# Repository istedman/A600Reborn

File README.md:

# A600Reborn

Amiga A600 schematics recaptured in KiCad and a new PCB design created from them. 
There is currently one, working, version which replaces the RF modulator with a mini-DIN for S-video.

Schematics and baseline PCB captured by Mick @ EAB. Checked and updated by myself.

Original thread is here: http://eab.abime.net/showthread.php?t=98176

<B>Status as of 23rd February 2021</B><P>
  
The Baseline version is still undergoing testing and is currently not fully functioning, this vairant is not published here.
Use the A600_S_Video branch if you want to try the working variant.

The S-Video variant, which was tracked via manual methods, rather than auto-routed, currently works and boots.
<B> Photos of the S-Video variant<B>

Wiki will be updated with debug/test information.

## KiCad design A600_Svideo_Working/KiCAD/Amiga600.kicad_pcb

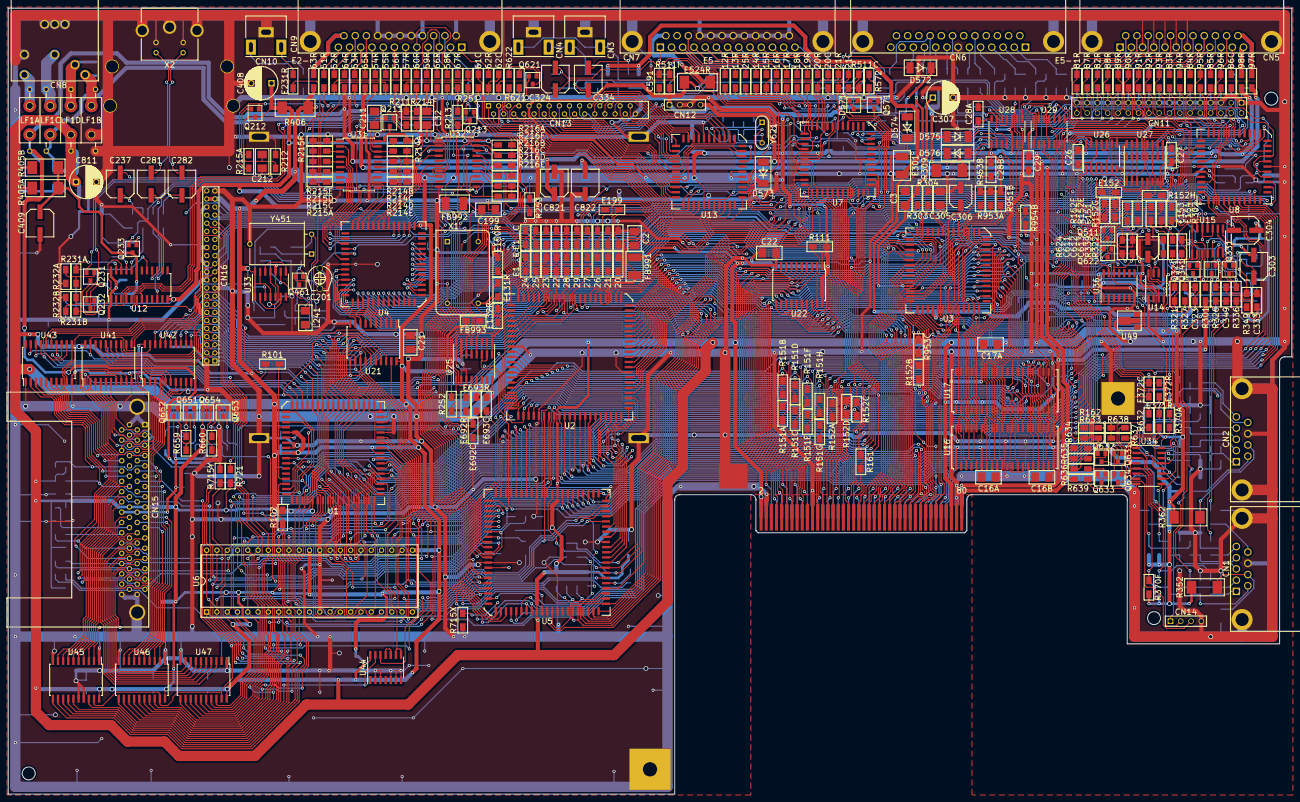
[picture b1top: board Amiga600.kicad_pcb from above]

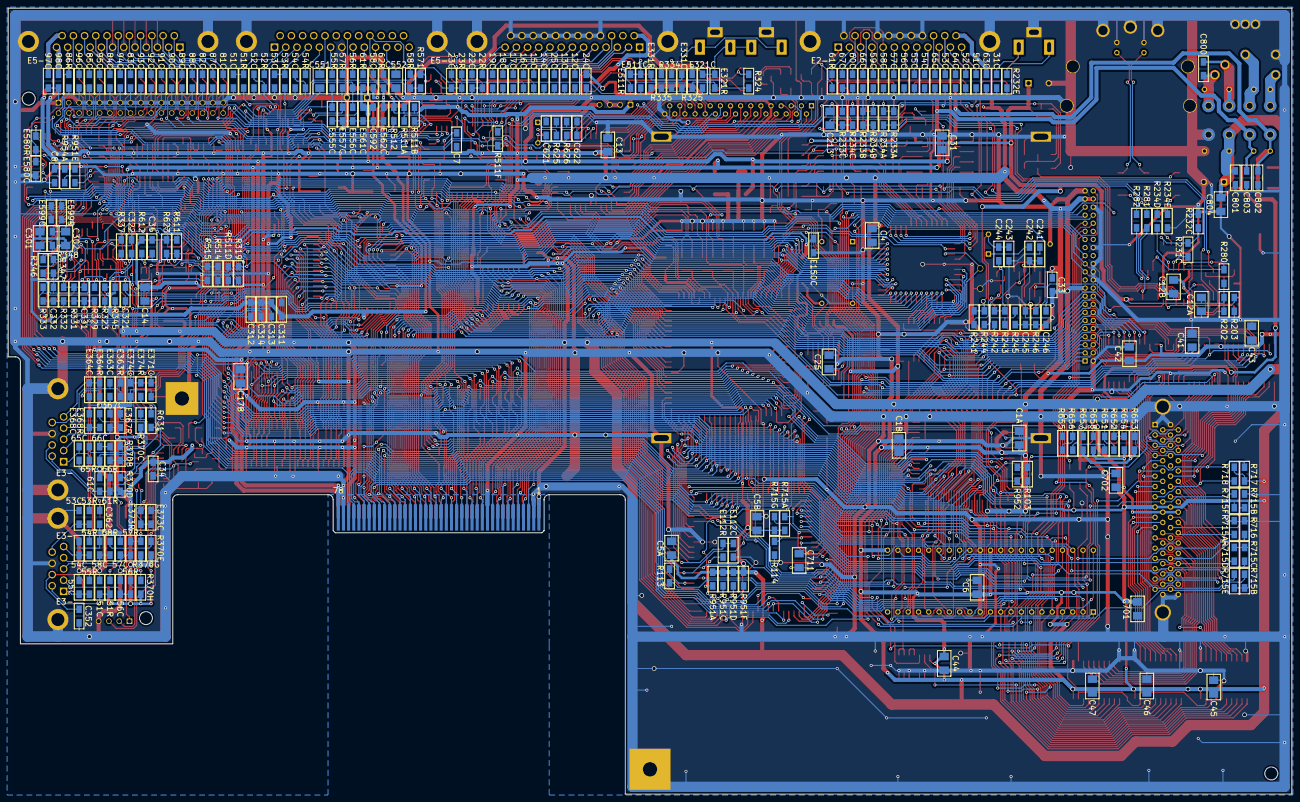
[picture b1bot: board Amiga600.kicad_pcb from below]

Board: 2 copper layers, 317.0 x 194.1 mm, 575 parts (259 on the bottom side), 566 nets.

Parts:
C2, C3, C4, C6, C13, C14, C21, C22, C25, C31, C32, C41, C42, C43, C44, C45, C46, C47, C199, C211, C212, C213, C301, C302, C305, C551, C552, C701, C702, C711, C804: 0.33uF; SMD_1210
C7, C8, C26, C27, C29, C33, C34, C36, C244, C246, C349, C591, C592, C613, C800, C801, C802, C803: 0.01uF; SMD_1206
C201: 47pf*; Trimmer
C237, C281, C282: 220uF; C_SMD_D6.3
C241, C245: 56pF; SMD_1206
C242: 15pF; SMD_1206
C243: 1000pF; SMD_1206
C303, C304, C324, C334: 22uF; C_SMD_D6.3
C306, C612: 10uF; C_SMD_D5
C307: 470uF; C_RAD_P5
C311, C312, C313, C314, C352: 0.047uF; SMD_1206
C321, C323, C331, C333: 3900pF; SMD_1206
C322, C332: 6800pF; SMD_1206
C362, C611: 0.1uF; SMD_1206
C408, C811: 1000uF; C_RAD_P5
C409: 100uF; C_SMD_D6.3
C621, C622: 22pF; SMD_1206
C821, C822: 47uF; C_SMD_D6.3
CA1, CA5, CA12, CA16, CA17: 0.33uF; SMD_1210
CA28: 0.01uF; SMD_1206
CB1, CB5, CB12, CB16, CB17: 0.33uF; SMD_1210
CB28: 0.01uF; SMD_1206
CN1, CN2: DB9P
CN3, CN4, CN10: RCA
CN5: DB23S
CN6: DB25P
CN7: DB25S
CN8: POWER; Power
CN9: DB23P
CN11: FLOPPY; Floppy
CN12, CN14: 4PIN; 1x04_P2.54
CN13: KEYBOARD; FFC-30
CN15: PCMCIA
CN16: IDE
D571: 1N914; SOT-23_Diode
D572, D573, D574, D575, D576: 1N4001; SMD_MELF
E151, E152, E153, E154: 47pF; SMD_1206
E199: 27; SMD_1206
E301: FB; SMD_1812
EC112, EC122, EC123, EC124, EC125, EC126, EC127: 22pF; SMD_1206
EC120: 0.33uF; SMD_1206
EC121, EC262: *; SMD_1206
EC128, EC129, EC150, EC258, EC259, EC260, EC692, EC693: 47pF; SMD_1206
EC231, EC251, EC252, EC253, EC254, EC255, EC256, EC257, EC261, EC266, EC267, EC511, EC512, EC513, EC514, EC515, EC516, EC517, EC518, EC519, EC520, EC521, EC522, EC523, EC525, EC551, EC552, EC558, EC580, EC581, EC582, EC583, EC584, EC585, EC586, EC587, EC588, EC589, EC590, EC591, EC592, EC593, EC594, EC595, EC596, EC599: 100pF; SMD_1206
EC263, EC264, EC265, EC524, EC557, EC561, EC562, EC597, EC598: 0.01uF; SMD_1206
EC321, EC331, EC355, EC356, EC357, EC358, EC365, EC366, EC367, EC368: 6800pF; SMD_1206
EC351, EC353, EC354, EC361, EC363, EC364, EC371, EC372, EC373, EC374, EC553, EC554, EC555, EC556: 470pF; SMD_1206
ER112, ER122, ER123, ER124, ER125, ER128, ER129, ER150, ER580, ER583, ER584, ER585, ER587, ER590, ER591, ER592, ER593, ER594, ER595, ER599: 27; SMD_1206
ER120, ER321, ER331: 0; SMD_1206
ER121: *; SMD_1206
ER126, ER127, ER253, ER254, ER255, ER256, ER557, ER561, ER562: 47; SMD_1206
ER131, ER132, ER251, ER252, ER257, ER261, ER262, ER266, ER267, ER351, ER353, ER354, ER355, ER356, ER357, ER358, ER361, ER363, ER364, ER365, ER366, ER367, ER368, ER371, ER372, ER373, ER374, ER511, ER512, ER513, ER514, ER515, ER516, ER517, ER518, ER519, ER520, ER521, ER522, ER523, ER525, ER551, ER552, ER553, ER554, ER555, ER556, ER558, ER581, ER582, ER586, ER588, ER589, ER596, ER692, ER693: 68; SMD_1206
ER231: FB100; SMD_1206
ER258, ER259, ER260, ER263, ER264, ER265, ER597, ER598: FB200; SMD_1206
ER524: 47; SMD_2512
FB991, FB992: FB; SMD_1812
FB993: FB; SMD_1206
H1, H2, H3: MountingHole; Hole
L241: 1.2uH; SMD_1210
LF1: FERRITE; Ferrite
MT1, MT2, MT3, MT4: MountingHole_Pad; MT1-4
MT5: MountingHole_Pad; MT5
MT6: MountingHole_Pad; MT6
MT7: MountingHole_Pad; MT7
P9: 80PIN; Expansion
Q211, Q212, Q213, Q231, Q232, Q233, Q461, Q511, Q571, Q621, Q622, Q651, Q653: 2N3904; SOT-23
Q321, Q331: MPF102; SOT-23
Q341, Q631, Q632, Q633, Q634, Q652, Q654: 2N3906; SOT-23
R101, R102, R103, R244, R303, R304, R319, R324, R334, R512, R621, R654: 1K; SMD_1206
R111, R161, R162, R515, R659, R660, R952: 470; SMD_1206
R113, R114: 27; SMD_1206
R202, R246, R624, R625, R626, R658: *; SMD_1206
R203: 0; SMD_1206
R211, R212, R213: 150; SMD_1206
R241, R251, R252, R253, R348, R514, R632, R634, R636, R638, R651, R655, R721: 4.7K; SMD_1206
R242: 6.8K; SMD_1206
R243, R322, R323, R327, R329, R332, R333, R337, R339, R346, R572, R623, R631, R633, R635, R637, R652, R653, R656, R657, R716, R717, R718: 10K; SMD_1206
R245, R347, R571: 2.7K; SMD_1206
R280: 2.61K; SMD_1206
R281, R282: 75; SMD_1206
R301, R302: 10; SMD_1206
R309: 1; SMD_2512
R321, R331: 680; SMD_1206
R325, R335: 2K; SMD_1206
R326, R336: 470K; SMD_1206
R345: 22K; SMD_1206
R349: 33K; SMD_1206
R352, R362, R406: 4.7; SMD_2512
R611: 1M; SMD_1206
R612: 47K; SMD_1206
R622, R639: 100; SMD_1206
RA151, RA152: 68; SMD_1206
RA214, RA215, RA216: 270; SMD_1206
RA231, RA954: 1K; SMD_1206
RA232: 33K; SMD_1206
RA233: 150; SMD_1206
RA234: 75; SMD_1206
RA370, RA951: 4.7K; SMD_1206
RA405: 1; SMD_2512
RA511, RA715: 10K; SMD_1206
RA714: 120; SMD_1206
RA953: 470; SMD_1206
RB151: 68; SMD_1206
RB152: 27; SMD_1206
RB214, RB215, RB216, RB231, RB954: 1K; SMD_1206
RB232: 33K; SMD_1206
RB233: 150; SMD_1206
RB234: 75; SMD_1206
RB370, RB951: 4.7K; SMD_1206
RB405: 1; SMD_2512
RB511, RB715: 10K; SMD_1206
RB714: 120; SMD_1206
RB953: 470; SMD_1206
RC151: 68; SMD_1206
RC152: 27; SMD_1206
RC214, RC215, RC216: 2K; SMD_1206
RC231: 1K; SMD_1206
RC232: 33K; SMD_1206
RC233: 150; SMD_1206
RC234: 75; SMD_1206
RC370, RC951: 4.7K; SMD_1206
RC511, RC715: 10K; SMD_1206
RC953: 470; SMD_1206
RD151: 68; SMD_1206
RD152: 27; SMD_1206
RD214, RD215, RD216: 4K; SMD_1206
RD234: 43; SMD_1206
RD370, RD951: 4.7K; SMD_1206
RD511: 1K; SMD_1206
RD715: 10K; SMD_1206
RE151: 68; SMD_1206
RE152: 27; SMD_1206
RE214, RE215, RE216: 8K; SMD_1206
RE232: 75; SMD_1206
RE234: 240; SMD_1206
RE370, RE951: 4.7K; SMD_1206
RE715: 10K; SMD_1206
RF151: 68; SMD_1206
RF152: 27; SMD_1206
RF214, RF215, RF216: 330; SMD_1206
RF370, RF951: 4.7K; SMD_1206
RF511, RF715: 10K; SMD_1206
RG151: 68; SMD_1206
RG152: 27; SMD_1206
RG370: 4.7K; SMD_1206
RG715: 10K; SMD_1206
RH151: 68; SMD_1206
RH152: 27; SMD_1206
RH370: 4.7K; SMD_1206
RI511: 10K; SMD_1206
RX715: 4.7K; SMD_1206
RY715: 4.7K; SMD_1206
U1: MC68000; PLCC-68
U2: AGNUS; PLCC-84
U3: PAULA; PLCC-52
U4: DENISE; PLCC-52
U5: GAYLE; PLCC-84
U6: ROM; DIP-42
U7, U8: 8520; PLCC-44
U12: CXA2075M; SOP-24
U13: 6570; PLCC-44
U14: NE555; SOIC-8
U15: TL084; SOIC-14
U16, U17: 256Kx16; SOJ-40
U21, U22, U41, U42, U43, U45, U46, U47: 74LS245; SOIC-20W
U25: 74F258; SOIC-16-DUAL
U26: 74F00; SOIC-14
U27: 74F139; SOIC-16-DUAL
U28: 1488; SOIC-14
U29: 1489; SOIC-14
U31, U32: 74HCT244; SOIC-20W
U33: 74LS74A; SOIC-14
U34: 74LS157; SOIC-16
U36: 74F27; SOIC-14
U44: 74F02; SOIC-14
U49: RH5VA43A; SOT-89
X1: 28.37516MHz; Oscillator
X2: MINI-DIN; S-Video
Y451: 4.433619MHz; Crystal
Y621: 3MHz; Resonator

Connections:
7MHz: EC123.2, ER123.2, U1.15
7MHz_A: C201.1, EC122.2, ER122.2, U4.38
14MHz: E199.2, EC121.2, ER121.2, U5.22
14MHz_A: EC120.2, ER120.2, P9.67
+5V: C4.1, C6.1, C7.1, C8.1, C13.1, C14.1, C21.1, C22.1, C26.1, C27.1, C29.1, C33.1, C34.1, C36.1, C41.1, C42.1, C43.1, C44.1, C45.1, C46.1, C47.1, C591.1, C701.1, C801.1, C804.1, C811.1, CA1.1, CA5.1, CA16.1, CA17.1, CB1.1, CB5.1, CB16.1, CB17.1, CN12.1, CN13.9, CN15.17, CN15.51, CN16.41, CN16.42, D572.1, D573.1, D574.1, EC524.2, ER263.2, ER524.2, ER598.1, FB991.1, FB992.1, FB993.1, LF1.8, P9.1, P9.2, P9.76, Q631.2, Q632.2, Q633.2, Q634.2, Q654.2, R101.1, R102.1, R103.1, R111.1, R251.1, R252.1, R253.1, R309.1, R319.2, R352.1, R362.1, R406.1, R512.1, R514.1, R611.1, R612.1, R623.1, R631.1, R633.1, R635.1, R637.1, R639.1, R658.1, R716.1, R717.1, R718.1, R721.1, R952.2, RA370.1, RA405.2, RA511.1, RA715.1, RA951.2, RA953.2, RA954.2, RB370.1, RB405.2, RB511.1, RB715.1, RB951.2, RB953.2, RB954.2, RC370.1, RC511.1, RC715.1, RC951.2, RC953.2, RD370.1, RD511.1, RD715.1, RD951.2, RE370.1, RE715.1, RE951.2, RF370.1, RF511.1, RF715.1, RF951.2, RG370.1, RG715.1, RH370.1, RI511.1, U1.14, U1.18, U1.31, U1.52, U4.21, U5.20, U5.62, U6.22, U6.32, U7.22, U8.22, U13.1, U13.24, U13.33, U13.44, U14.4, U14.8, U16.1, U16.6, U16.20, U17.1, U17.6, U17.20, U21.20, U22.20, U26.14, U27.16, U28.5, U28.10, U28.13, U29.14, U33.1, U33.4, U33.10, U33.13, U33.14, U34.16, U36.14, U41.20, U42.20, U43.20, U44.14, U45.20, U46.20, U47.20, U49.2
+12V: C592.1, C802.1, C821.1, CN12.4, D575.2, EC561.1, ER264.2, ER561.1, ER597.1, LF1.2, P9.79, Q652.2, R301.1, R653.1, R657.1
+AV: C301.1, C303.1, Q341.2, R301.2, R347.1, U15.4
+VID: C31.1, C32.1, C408.1, CA12.1, Q211.3, Q212.3, Q213.3, R202.1, R241.1, R244.1, R280.1, R406.2, RA214.1, RA215.1, RA216.1, U12.12, U31.20, U32.20
+VOUT: C409.1, CB12.1, Q231.3, Q232.3, Q233.3, RA405.1, RB405.1, U12.19
-12V: C803.2, C822.2, D576.1, EC562.1, ER265.2, ER562.1, LF1.6, P9.80, R302.2
-AV: C302.2, C304.2, R302.1, R348.2, U15.11
/06. Serial, Parallel/PPD0: ER512.1, U7.12
/06. Serial, Parallel/PPD1: ER513.1, U7.13
/06. Serial, Parallel/PPD2: ER514.1, U7.14
/06. Serial, Parallel/PPD3: ER515.1, U7.15
/06. Serial, Parallel/PPD4: ER516.1, U7.16
/06. Serial, Parallel/PPD5: ER517.1, U7.17
/06. Serial, Parallel/PPD6: ER518.1, U7.18
/06. Serial, Parallel/PPD7: ER519.1, U7.19
/10. PCMCIA/CC_A0: CN15.29, U45.2
/10. PCMCIA/CC_A1: CN15.28, U47.9
/10. PCMCIA/CC_A2: CN15.27, U47.8
/10. PCMCIA/CC_A3: CN15.26, U47.7
/10. PCMCIA/CC_A4: CN15.25, U47.6
/10. PCMCIA/CC_A5: CN15.24, U47.5
/10. PCMCIA/CC_A6: CN15.23, U47.4
/10. PCMCIA/CC_A7: CN15.22, U47.3
/10. PCMCIA/CC_A8: CN15.12, U47.2
/10. PCMCIA/CC_A9: CN15.11, U46.9
/10. PCMCIA/CC_A10: CN15.8, U46.8
/10. PCMCIA/CC_A11: CN15.10, U46.7
/10. PCMCIA/CC_A12: CN15.21, U46.6
/10. PCMCIA/CC_A13: CN15.13, U46.5
/10. PCMCIA/CC_A14: CN15.14, U46.4
/10. PCMCIA/CC_A15: CN15.20, U46.3
/10. PCMCIA/CC_A16: CN15.19, U46.2
/10. PCMCIA/CC_A17: CN15.46, U45.9
/10. PCMCIA/CC_A18: CN15.47, U45.8
/10. PCMCIA/CC_A19: CN15.48, U45.7
/10. PCMCIA/CC_A20: CN15.49, U45.6
/10. PCMCIA/CC_A21: CN15.50, U45.5
/10. PCMCIA/CC_A22: CN15.53, U45.4
/10. PCMCIA/CC_A23: CN15.54, U45.3
/10. PCMCIA/CC_A24: CN15.55, RB714.2
/10. PCMCIA/CC_A25: CN15.56, RA714.2
/10. PCMCIA/CC_D0: CN15.30, U41.9
/10. PCMCIA/CC_D1: CN15.31, U41.8
/10. PCMCIA/CC_D2: CN15.32, U41.7
/10. PCMCIA/CC_D3: CN15.2, U41.6
/10. PCMCIA/CC_D4: CN15.3, U41.5
/10. PCMCIA/CC_D5: CN15.4, U41.4
/10. PCMCIA/CC_D6: CN15.5, U41.3
/10. PCMCIA/CC_D7: CN15.6, U41.2
/10. PCMCIA/CC_D8: CN15.64, U42.9
/10. PCMCIA/CC_D9: CN15.65, U42.8
/10. PCMCIA/CC_D10: CN15.66, U42.7
/10. PCMCIA/CC_D11: CN15.37, U42.6
/10. PCMCIA/CC_D12: CN15.38, U42.5
/10. PCMCIA/CC_D13: CN15.39, U42.4
/10. PCMCIA/CC_D14: CN15.40, U42.3
/10. PCMCIA/CC_D15: CN15.41, U42.2
A1: U1.32, U2.60, U6.10, U47.11
A2: CN16.35, P9.57, U1.33, U2.61, U6.9, U47.12
A3: CN16.33, P9.58, U1.34, U2.62, U6.8, U47.13
A4: CN16.36, P9.59, U1.35, U2.63, U6.7, U47.14
A5: P9.60, U1.36, U2.64, U6.6, U47.15
A6: U1.37, U2.65, U6.5, U47.16
A7: U1.38, U2.66, U6.4, U47.17
A8: U1.39, U2.67, U6.3, U7.42, U8.42, U47.18
A9: U1.40, U2.68, U6.41, U7.41, U8.41, U46.11
A10: U1.41, U2.69, U6.40, U7.39, U8.39, U46.12
A11: U1.42, U2.70, U6.39, U7.38, U8.38, U46.13
A12: U1.43, U2.71, U5.41, U6.38, U46.14
A13: U1.44, U2.72, U5.42, U6.37, U46.15
A14: U1.45, U2.73, U5.43, U6.36, U46.16
A15: U1.46, U2.74, U5.44, U6.35, U46.17
A16: U1.47, U2.75, U5.46, U6.34, U44.8, U44.9, U46.18
A17: U1.48, U2.76, U5.47, U6.33, U45.11
A18: U1.49, U2.77, U5.48, U6.2, U45.12
A19: U1.50, U2.59, U5.49, U6.1, U45.13
A20: U1.51, U2.35, U5.50, U6.42, U45.14
A21: U1.53, U5.51
A22: U1.54, U5.52
A23: U1.55, U5.53, U45.15
AB: ER258.1, RC234.2
AG: ER259.1, RB234.2
AR: ER260.1, RA234.2
AUDIN: C551.2, R339.1
AUDIO: C301.2, C302.1, C303.2, C304.1, C311.2, C312.2, C313.2, C314.2, C323.2, C333.2, C349.2, E301.1, R325.2, R335.2, R345.2, U3.37
AUDOUT: C324.2, C552.2, R324.1
AVREF: C305.1, C306.1, R303.2, R304.1, U15.10, U15.12
BDRA0: P9.23, RA151.2, U16.16, U17.16
BDRA1: P9.24, RB151.2, U16.17, U17.17
BDRA2: P9.25, RC151.2, U16.18, U17.18
BDRA3: P9.26, RD151.2, U16.19, U17.19
BDRA4: P9.27, RE151.2, U16.22, U17.22
BDRA5: P9.28, RF151.2, U16.23, U17.23
BDRA6: P9.29, RG151.2, U16.24, U17.24
BDRA7: P9.30, RH151.2, U16.25, U17.25
BDRA8: P9.31, RA152.2, U16.26, U17.26
B[0]: ER257.1, RE216.1, U32.12
B[3]: ER256.1, RB216.1, U32.18
CCK: EC127.2, ER127.2, P9.69, U3.31, U4.39, U5.23, U25.5, U25.6, U32.11
CCKQ: EC129.2, ER129.2, U3.32
CCKQ_A: EC128.2, ER128.2, R246.1, U33.3, U34.1
CCK_A: EC126.2, ER126.2, U26.2, U26.12, U27.1, U27.15
CCK_B: ER266.2, U32.9
CC_RESET: CN15.58, RY715.1, U5.5
D0: CN16.4, P9.49, U1.5, U6.14, U7.36, U22.11, U42.11
D1: CN16.6, P9.50, U1.4, U6.16, U7.35, U22.12, U42.12
D2: CN16.8, P9.51, U1.3, U6.18, U7.34, U22.13, U42.13
D3: CN16.10, P9.52, U1.2, U6.20, U7.33, U22.14, U42.14
D4: CN16.12, P9.53, U1.1, U6.23, U7.32, U22.15, U42.15
D5: CN16.14, P9.54, U1.68, U6.25, U7.31, U22.16, U42.16
D6: CN16.16, P9.55, U1.67, U6.27, U7.30, U22.17, U42.17
D7: CN16.18, P9.56, U1.66, U6.29, U7.29, U22.18, U42.18
D8: CN16.17, U1.65, U5.61, U6.15, U8.36, U21.18, U41.11
D9: CN16.15, U1.64, U5.60, U6.17, U8.35, U21.17, U41.12
D10: CN16.13, U1.63, U5.59, U6.19, U8.34, U21.16, U41.13
D11: CN16.11, U1.62, U5.58, U6.21, U8.33, U21.15, U41.14
D12: CN16.9, U1.61, U5.57, U6.24, U8.32, U21.14, U41.15
D13: CN16.7, U1.60, U5.56, U6.26, U8.31, U21.13, U41.16
D14: CN16.5, U1.59, U5.55, U6.28, U8.30, U21.12, U41.17
D15: CN16.3, U1.58, U5.54, U6.30, U8.29, U21.11, U41.18
DIR: ER593.1, U8.13
DKWE: U3.42, U5.69
DMAL: U2.18, U3.12
DRA0: RA151.1, U2.42
DRA1: RB151.1, U2.43
DRA2: RC151.1, U2.44
DRA3: RD151.1, U2.45
DRA4: RE151.1, U2.46
DRA5: RF151.1, U2.47
DRA6: RG151.1, U2.48
DRA7: RH151.1, U2.49
DRA8: RA152.1, U2.50
DRA9: U2.55, U25.10, U25.11, U26.13
DRD0: P9.5, U2.14, U3.10, U4.8, U16.2, U17.2, U22.9
DRD1: P9.6, U2.13, U3.9, U4.6, U16.3, U17.3, U22.8
DRD2: P9.7, U2.12, U3.7, U4.5, U16.4, U17.4, U22.7
DRD3: P9.8, U2.11, U3.6, U4.4, U16.5, U17.5, U22.6
DRD4: P9.9, U2.10, U3.5, U4.3, U16.7, U17.7, U22.5
DRD5: P9.10, U2.9, U3.4, U4.2, U16.8, U17.8, U22.4
DRD6: P9.11, U2.8, U3.3, U4.1, U16.9, U17.9, U22.3
DRD7: P9.12, U2.7, U3.2, U4.52, U16.10, U17.10, U22.2
DRD8: P9.13, U2.6, U3.1, U4.51, U16.31, U17.31, U21.2
DRD9: P9.14, U2.5, U3.52, U4.50, U16.32, U17.32, U21.3
DRD10: P9.15, U2.4, U3.51, U4.49, U16.33, U17.33, U21.4
DRD11: P9.16, U2.3, U3.50, U4.48, U16.34, U17.34, U21.5
DRD12: P9.17, U2.2, U3.49, U4.46, U16.36, U17.36, U21.6
DRD13: P9.18, U2.1, U3.48, U4.45, U16.37, U17.37, U21.7
DRD14: P9.19, U2.84, U3.46, U4.44, U16.38, U17.38, U21.8
DRD15: P9.20, U2.83, U3.45, U4.43, U16.39, U17.39, U21.9
E: EC112.2, ER112.2, R626.1, U7.27, U8.27
GND: C2.2, C3.2, C4.2, C6.2, C7.2, C8.2, C13.2, C14.2, C21.2, C22.2, C25.2, C26.2, C27.2, C29.2, C31.2, C32.2, C33.2, C34.2, C36.2, C41.2, C42.2, C43.2, C44.2, C45.2, C46.2, C47.2, C199.2, C201.2, C241.2, C243.2, C245.2, C305.2, C306.2, C307.2, C352.1, C362.1, C408.2, C409.2, C591.2, C592.2, C611.2, C612.2, C613.2, C621.1, C622.1, C701.2, C702.2, C801.2, C802.2, C803.1, C804.2, C811.2, C821.2, C822.1, CA1.2, CA5.2, CA12.2, CA16.2, CA17.2, CA28.2, CB1.2, CB5.2, CB12.2, CB16.2, CB17.2, CB28.2, CN1.0, CN1.8, CN2.0, CN2.8, CN3.3, CN4.3, CN5.0, CN5.3, CN5.4, CN5.5, CN5.6, CN5.7, CN6.0, CN6.7, CN7.0, CN7.17, CN7.18, CN7.19, CN7.20, CN7.21, CN7.22, CN7.23, CN7.24, CN7.25, CN8.0, CN8.2, CN9.0, CN9.13, CN9.16, CN9.17, CN9.18, CN9.19, CN9.20, CN10.3, CN11.1, CN11.5, CN11.7, CN11.9, CN11.11, CN11.13, CN11.15, CN11.17, CN11.19, CN11.21, CN11.23, CN11.25, CN11.27, CN11.29, CN11.31, CN11.33, CN12.2, CN12.3, CN13.30, CN14.4, CN15.0, CN15.1, CN15.34, CN15.35, CN15.68, CN16.2, CN16.19, CN16.22, CN16.24, CN16.26, CN16.30, CN16.40, CN16.43, D571.2, E151.2, E152.2, E153.2, E154.2, E301.2, EC112.1, EC120.1, EC121.1, EC122.1, EC123.1, EC124.1, EC125.1, EC126.1, EC127.1, EC128.1, EC129.1, EC150.1, EC231.1, EC251.1, EC252.1, EC253.1, EC254.1, EC255.1, EC256.1, EC257.1, EC258.1, EC259.1, EC260.1, EC261.2, EC262.2, EC263.2, EC264.2, EC265.2, EC266.2, EC267.2, EC321.1, EC331.1, EC351.1, EC353.1, EC354.1, EC355.2, EC356.2, EC357.2, EC358.2, EC361.1, EC363.1, EC364.1, EC365.2, EC366.2, EC367.2, EC368.2, EC371.1, EC372.1, EC373.1, EC374.1, EC511.1, EC512.1, EC513.1, EC514.1, EC515.1, EC516.1, EC517.1, EC518.1, EC519.1, EC520.2, EC521.2, EC522.2, EC523.2, EC524.1, EC525.2, EC551.1, EC552.2, EC553.1, EC554.2, EC555.2, EC556.2, EC557.1, EC558.2, EC561.2, EC562.2, EC580.1, EC581.1, EC582.1, EC583.1, EC584.1, EC585.1, EC586.1, EC587.1, EC588.1, EC589.1, EC590.1, EC591.1, EC592.1, EC593.1, EC594.1, EC595.1, EC596.1, EC597.1, EC598.1, EC599.1, EC692.1, EC693.1, L241.2, LF1.4, MT1.1, MT2.1, MT3.1, MT4.1, MT5.1, MT6.1, MT7.1, P9.3, P9.4, P9.21, P9.22, P9.77, P9.78, Q461.2, Q511.2, Q571.2, Q621.2, Q622.2, Q651.2, Q653.2, R161.2, R162.2, R203.2, R211.2, R212.2, R213.2, R242.2, R304.2, R572.2, R652.2, R654.2, R656.2, RA232.2, RA233.2, RA714.1, RB232.2, RB233.2, RB714.1, RC232.2, RC233.2, RE232.2, RE234.2, RF214.1, RF215.1, RF216.1, RX715.2, RY715.2, U1.16, U1.17, U1.56, U1.57, U2.41, U2.58, U2.82, U3.8, U4.40, U5.3, U5.24, U5.45, U5.66, U6.12, U6.31, U7.1, U8.1, U12.1, U12.24, U13.13, U14.1, U16.21, U16.35, U16.40, U17.21, U17.35, U17.40, U21.10, U22.10, U25.2, U25.3, U25.8, U25.15, U26.7, U27.8, U28.7, U29.7, U31.1, U31.10, U31.19, U32.1, U32.10, U32.19, U33.7, U34.8, U34.15, U36.7, U41.10, U42.10, U43.1, U43.10, U44.2, U44.3, U44.5, U44.6, U44.7, U45.1, U45.10, U45.16, U45.17, U46.1, U46.10, U47.1, U47.10, U49.3, X1.7, X2.0, X2.1, X2.2, Y451.3
G[3]: ER255.1, RB215.1, U31.9
LEFT: C321.1, P9.65, R321.1, U3.34, U15.13
M0H: EC372.2, ER372.2, U4.10
M0V: EC371.2, ER371.2, U4.41
M1H: EC374.2, ER374.2, U4.9
M1V: EC373.2, ER373.2, U4.42
MONO: R327.1, R337.2, R345.1
NOISE: C711.2, R329.1
unnamed: C2.1, FB991.2, U2.15
unnamed: C3.1, C307.1, R303.1, R309.2, U3.30
unnamed: C25.1, FB993.2, U25.16
unnamed: C199.1, FB992.2, X1.14
unnamed: C211.1, Q211.2, R211.1
unnamed: C211.2, U12.2
unnamed: C212.1, Q212.2, R212.1
unnamed: C212.2, U12.3
unnamed: C213.1, Q213.2, R213.1
unnamed: C213.2, U12.4
unnamed: C237.1, RD234.2, RE234.1
unnamed: C237.2, ER231.1
unnamed: C241.1, C242.1, R241.2, U33.9
unnamed: C242.2, Y451.1
unnamed: C243.1, C244.1, L241.1, Y451.2
unnamed: C244.2, Q461.1, R242.1, R243.1
unnamed: C245.1, C246.1, R245.2, R246.2
unnamed: C246.2, U12.6
unnamed: C281.1, R281.2
unnamed: C281.2, X2.3
unnamed: C282.1, R282.2
unnamed: C282.2, X2.4
unnamed: C311.1, ER354.1, U3.35
unnamed: C312.1, ER353.1, U3.36
unnamed: C313.1, ER364.1, U3.38
unnamed: C314.1, ER363.1, U3.39
unnamed: C321.2, Q321.1, R321.2, R322.1, U15.14
unnamed: C322.1, C324.1, R327.2, U15.1, U15.2
unnamed: C322.2, R322.2, R323.1
unnamed: C323.1, Q321.2, R323.2, U15.3
unnamed: C331.2, Q331.1, R331.2, R332.1, U15.8
unnamed: C332.1, C334.1, R337.1, U15.6, U15.7
unnamed: C332.2, R332.2, R333.1
unnamed: C333.1, Q331.2, R333.2, U15.5
unnamed: C334.2, R334.1
unnamed: C349.1, R326.1, R336.1, R349.2
unnamed: C352.2, CN1.7, R352.2
unnamed: C362.2, CN2.7, R362.2
unnamed: C551.1, CN6.18
unnamed: C552.1, CN6.11
unnamed: C611.1, Q622.3, R611.2, R624.2, U14.2
unnamed: C612.1, R612.2, U14.6, U14.7
unnamed: C613.1, U14.5
unnamed: C621.2, U13.12, Y621.2
unnamed: C622.2, R625.2, R626.2, U13.11, Y621.1
unnamed: C711.1, U5.4
unnamed: C800.1, CN8.4, LF1.3
unnamed: C800.2, CN8.1, LF1.7
unnamed: CA28.1, D575.1, U28.14
unnamed: CB28.1, D576.2, U28.1
unnamed: CN1.1, EC355.1, ER355.1
unnamed: CN1.2, EC356.1, ER356.1
unnamed: CN1.3, EC357.1, ER357.1
unnamed: CN1.4, EC358.1, ER358.1
unnamed: CN1.5, EC354.2, ER354.2
unnamed: CN1.6, EC351.2, ER351.2
unnamed: CN1.9, EC353.2, ER353.2
unnamed: CN2.1, EC365.1, ER365.1
unnamed: CN2.2, EC366.1, ER366.1
unnamed: CN2.3, EC367.1, ER367.1
unnamed: CN2.4, EC368.1, ER368.1
unnamed: CN2.5, EC364.2, ER364.2
unnamed: CN2.6, EC361.2, ER361.2
unnamed: CN2.9, EC363.2, ER363.2
unnamed: CN3.1, CN4.2, EC321.2, ER321.2
unnamed: CN3.2, CN4.1, EC331.2, ER331.2
unnamed: CN5.8, EC583.2, ER583.2
unnamed: CN5.9, EC584.2, ER584.2
unnamed: CN5.10, EC585.2, ER585.2
unnamed: CN5.12, EC598.2, ER598.2
unnamed: CN5.20, EC594.2, ER594.2
unnamed: CN5.23, EC597.2, ER597.2
unnamed: CN6.2, EC551.2, ER551.2
unnamed: CN6.3, ER552.2
unnamed: CN6.4, EC553.2, ER553.2
unnamed: CN6.5, ER554.2
unnamed: CN6.6, ER555.2
unnamed: CN6.8, ER556.2
unnamed: CN6.9, ER561.2
unnamed: CN6.10, ER562.2
unnamed: CN6.20, ER557.1
unnamed: CN6.22, EC558.1, ER558.1
unnamed: CN7.1, EC511.2, ER511.2
unnamed: CN7.2, EC512.2, ER512.2
unnamed: CN7.3, EC513.2, ER513.2
unnamed: CN7.4, EC514.2, ER514.2
unnamed: CN7.5, EC515.2, ER515.2
unnamed: CN7.6, EC516.2, ER516.2
unnamed: CN7.7, EC517.2, ER517.2
unnamed: CN7.8, EC518.2, ER518.2
unnamed: CN7.9, EC519.2, ER519.2
unnamed: CN7.10, ER520.2
unnamed: CN7.11, ER521.2
unnamed: CN7.12, ER522.2
unnamed: CN7.13, ER523.2
unnamed: CN7.14, ER524.1
unnamed: CN7.16, EC525.1, ER525.1
unnamed: CN8.3, LF1.1
unnamed: CN8.5, LF1.5
unnamed: CN9.1, ER262.2
unnamed: CN9.2, ER261.2
unnamed: CN9.3, EC260.2, ER260.2
unnamed: CN9.4, EC259.2, ER259.2
unnamed: CN9.5, EC258.2, ER258.2
unnamed: CN9.6, EC257.2, ER257.2
unnamed: CN9.7, EC256.2, ER256.2
unnamed: CN9.8, EC255.2, ER255.2
unnamed: CN9.9, EC254.2, ER254.2
unnamed: CN9.10, EC253.2, ER253.2
unnamed: CN9.11, EC252.2, ER252.2
unnamed: CN9.12, EC251.2, ER251.2
unnamed: CN9.14, EC267.1, ER267.1
unnamed: CN9.15, EC266.1, ER266.1
unnamed: CN9.21, EC265.1, ER265.1
unnamed: CN9.22, EC264.1, ER264.1
unnamed: CN9.23, EC263.1, ER263.1
unnamed: CN10.1, RE232.1
unnamed: CN10.2, EC231.2, ER231.2
unnamed: CN5.11, CN11.2, EC586.2, ER586.2
unnamed: CN5.22, CN11.8, EC596.2, ER596.2
unnamed: CN11.10, EC580.2, ER580.2
unnamed: CN5.21, CN11.12, EC595.2, ER595.2
unnamed: CN11.4, CN11.16, EC599.2, ER599.2
unnamed: CN5.19, CN11.18, EC593.2, ER593.2
unnamed: CN5.18, CN11.20, EC592.2, ER592.2
unnamed: CN5.17, CN11.22, EC591.2, ER591.2
unnamed: CN5.16, CN11.24, EC590.2, ER590.2
unnamed: CN5.15, CN11.26, EC589.2, ER589.2
unnamed: CN5.14, CN11.28, EC588.2, ER588.2
unnamed: CN5.2, CN11.30, EC582.2, ER582.2
unnamed: CN5.13, CN11.32, EC587.2, ER587.2
unnamed: CN5.1, CN11.34, EC581.2, ER581.2
unnamed: CN13.1, U13.40
unnamed: CN13.2, U13.38
unnamed: CN13.3, U13.37
unnamed: CN13.4, R622.1
unnamed: CN13.5, U13.36
unnamed: CN13.6, U13.32
unnamed: CN13.7, U13.35
unnamed: CN13.8, U13.31
unnamed: CN13.10, U13.30, U36.13
unnamed: CN13.11, U13.29, U36.1
unnamed: CN13.12, U13.28
unnamed: CN13.13, U13.27
unnamed: CN13.14, U13.26, U36.2
unnamed: CN13.15, U13.3
unnamed: CN13.16, U13.4
unnamed: CN13.17, U13.5
unnamed: CN13.18, U13.7
unnamed: CN13.19, U13.8
unnamed: CN13.20, U13.9
unnamed: CN13.21, U13.10
unnamed: CN13.22, U13.14
unnamed: CN13.23, U13.15
unnamed: CN13.24, U13.16
unnamed: CN13.25, U13.18
unnamed: CN13.26, U13.19
unnamed: CN13.27, U13.20
unnamed: CN13.28, U13.21
unnamed: CN13.29, U13.22
unnamed: CN14.1, Q631.3
unnamed: CN14.2, Q632.3, Q634.3
unnamed: CN14.3, Q633.3, R639.2
unnamed: CN16.44, R721.2
unnamed: D571.1, Q571.1, R571.1, R572.1
unnamed: D572.2, EC520.1, ER520.1, RF511.2, U7.26
unnamed: D573.2, ER511.1, RI511.2, U7.20
unnamed: E199.1, ER122.1, ER123.1, U2.37
unnamed: EC150.2, ER150.2, U26.1
unnamed: EC521.1, ER521.1, U8.2, U8.43
unnamed: EC522.1, ER522.1, U8.3, U8.44
unnamed: EC523.1, ER523.1, Q571.3, RC511.2, U8.4
unnamed: EC552.1, ER552.1, U29.1
unnamed: EC554.1, ER554.1, U29.4
unnamed: EC555.1, ER555.1, U29.10
unnamed: EC556.1, ER556.1, U29.13
unnamed: EC557.2, ER557.2, U28.11
unnamed: ER112.1, U5.10
unnamed: ER120.1, ER121.1, U2.40
unnamed: ER124.1, ER125.1, U2.36
unnamed: ER126.1, ER127.1, U2.39
unnamed: ER128.1, ER129.1, U2.38
unnamed: ER131.1, X1.8
unnamed: ER131.2, U25.13
unnamed: ER132.1, U25.12
unnamed: ER132.2, U2.34
unnamed: ER150.1, U25.9
unnamed: ER321.1, R324.2, R325.1
unnamed: ER331.1, R334.2, R335.1
unnamed: ER355.2, RH370.2, U34.2
unnamed: ER356.2, RF370.2, U34.5
unnamed: ER357.2, RG370.2, U34.3
unnamed: ER358.2, RE370.2, U34.6
unnamed: ER365.2, RD370.2, U34.11
unnamed: ER366.2, RB370.2, U34.14
unnamed: ER367.2, RC370.2, U34.10
unnamed: ER368.2, RA370.2, U34.13
unnamed: ER371.1, U34.4
unnamed: ER372.1, U34.7
unnamed: ER373.1, U34.9
unnamed: ER374.1, U34.12
unnamed: ER551.1, U28.8
unnamed: ER553.1, U28.6
unnamed: ER558.2, R571.2
unnamed: ER692.1, ER693.1, U25.7
unnamed: Q211.1, RA214.2, RB214.2, RC214.2, RD214.2, RE214.2, RF214.2
unnamed: Q212.1, RA215.2, RB215.2, RC215.2, RD215.2, RE215.2, RF215.2
unnamed: Q213.1, RA216.2, RB216.2, RC216.2, RD216.2, RE216.2, RF216.2
unnamed: Q231.1, RA231.2, RA232.1
unnamed: Q231.2, RA233.1, RA234.1
unnamed: Q232.1, RB231.2, RB232.1
unnamed: Q232.2, RB233.1, RB234.1
unnamed: Q233.1, RC231.2, RC232.1
unnamed: Q233.2, RC233.1, RC234.1
unnamed: Q321.3, R326.2
unnamed: Q331.3, R336.2
unnamed: Q341.1, R346.2, R347.2
unnamed: Q341.3, R348.1, R349.1
unnamed: Q461.3, R243.2, R244.2, R245.1
unnamed: Q511.1, R514.2, R515.2
unnamed: Q621.1, R621.2
unnamed: Q621.3, R622.2
unnamed: Q622.1, R623.2, U36.12
unnamed: Q631.1, R632.2
unnamed: Q632.1, R634.2
unnamed: Q633.1, R636.2
unnamed: Q634.1, R638.2
unnamed: Q651.1, R651.2, R652.1
unnamed: Q651.3, R653.2, R659.1
unnamed: Q652.1, R659.2
unnamed: Q653.1, R655.2, R656.1
unnamed: Q653.3, R657.2, R660.1
unnamed: Q654.1, R660.2
unnamed: R101.2, U1.13, U1.23
unnamed: R102.2, R114.1, U1.24
unnamed: R103.2, U1.12, U5.38
unnamed: R111.2, U5.27, U5.28, U21.19, U22.19
unnamed: R113.2, U5.37
unnamed: R114.2, U5.82
unnamed: R202.2, R203.1, U12.7
unnamed: R280.2, U12.17
unnamed: R281.1, U12.16
unnamed: R282.1, U12.15
unnamed: R346.1, U28.3
unnamed: R515.1, U14.3
unnamed: R621.1, U13.25
unnamed: R624.1, U13.34
unnamed: RA231.1, U12.23
unnamed: RB231.1, U12.22
unnamed: RC214.1, U31.16
unnamed: RC215.1, U31.7
unnamed: RC216.1, U32.16
unnamed: RC231.1, U12.21
unnamed: RD214.1, U31.14
unnamed: RD215.1, U31.5
unnamed: RD216.1, U32.14
unnamed: RD234.1, U12.20
unnamed: RE152.1, U27.4
unnamed: RE214.1, U31.12
unnamed: RE215.1, U31.3
unnamed: RF152.1, U27.5
unnamed: RG152.1, U27.12
unnamed: RH152.1, U27.11
unnamed: U2.19, U5.30
unnamed: U2.20, U5.29
unnamed: U2.23, U5.31
unnamed: U2.25, U5.32
unnamed: U26.3, U26.4
unnamed: U26.5, U26.8, U27.2, U27.14
unnamed: U26.6, U26.9
unnamed: U26.10, U26.11
unnamed: U8.10, U28.4
unnamed: U8.11, U28.12
unnamed: U8.8, U29.6
unnamed: U8.7, U29.8
unnamed: U8.9, U29.11
unnamed: U4.25, U31.2
unnamed: U4.24, U31.4
unnamed: U4.23, U31.6
unnamed: U4.22, U31.8
unnamed: U4.33, U31.11
unnamed: U4.32, U31.13
unnamed: U4.31, U31.15
unnamed: U4.30, U31.17
unnamed: U4.29, U32.2
unnamed: U4.28, U32.4
unnamed: U4.27, U32.6
unnamed: U4.26, U32.8
unnamed: U4.36, U32.13
unnamed: U33.2, U33.6
unnamed: U33.5, U33.11
unnamed: U33.8, U33.12
unnamed: U44.10, U44.11
unnamed: U44.13, U45.18
PE5: R655.1, U5.2
PE12: R651.1, U5.1
PIXELSW: ER267.2, U32.7
RGA1: P9.48, U2.33, U3.29, U4.18
RGA2: P9.47, U2.32, U3.28, U4.17
RGA3: P9.46, U2.31, U3.27, U4.16
RGA4: P9.45, U2.30, U3.26, U4.15
RGA5: P9.44, U2.29, U3.25, U4.14
RGA6: P9.43, U2.28, U3.24, U4.13
RGA7: P9.42, U2.27, U3.23, U4.12
RGA8: P9.41, U2.26, U3.22, U4.11
RIGHT: C331.1, P9.66, R329.2, R331.1, R339.2, U3.33, U15.9
R[3]: ER254.1, RB214.1, U31.18
R_W: RE951.1, U1.9, U2.22, U5.36, U7.24, U8.24, U21.1, U22.1, U41.1, U42.1
VPP: C702.1, CN15.18, CN15.52, Q652.3, Q654.3, R654.1, R658.2
XCLK: EC262.1, ER262.1, R253.2, U25.14
_AS: RF951.1, U1.6, U2.24, U5.33
_BCASL[0]: E151.1, P9.34, RE152.2, U16.29, U17.29
_BCASL[1]: E152.1, P9.35, RF152.2
_BCASU[0]: E153.1, P9.33, RG152.2, U16.28, U17.28
_BCASU[1]: E154.1, P9.36, RH152.2
_BRAS[0]: P9.37, RC152.2, U16.14
_BRAS[1]: P9.38, RD152.2, U17.14
_BWE: P9.39, RB152.2, U16.13, U17.13
_CASL: U2.53, U27.3
_CASU: U2.54, U27.13
_CCK: EC692.2, ER692.2, R625.1
_CCK_A: EC693.2, ER693.2
_CC_BUSY_IREQ: CN15.16, RF715.2, U5.80
_CC_BVD[1]: CN15.63, RC715.2, U5.77
_CC_BVD[2]: CN15.62, RD715.2, U5.78
_CC_CD[1]: CN15.36, RA715.2, U5.75
_CC_CD[2]: CN15.67, RB715.2, U5.76
_CC_CEL: CN15.42, U43.7
_CC_CEU: CN15.7, U43.6
_CC_ENA: R637.2, R638.1, U5.6, U41.19, U42.19, U43.19, U45.19, U46.19, U47.19
_CC_IORD: CN15.44, U43.4
_CC_IOWR: CN15.45, U43.5
_CC_OE: CN15.9, R717.2, U43.2
_CC_REG: CN15.61, U43.8
_CC_WAIT: CN15.59, R716.2, U43.11
_CC_WE_PGM: CN15.15, R718.2, U43.3
_CC_WP: CN15.33, RE715.2, U5.79
_CDAC: EC125.2, ER125.2, U4.37
_CDAC_A: EC124.2, ER124.2
_CHNG: ER586.1, U7.4
_CSYNC: U2.80, U4.35, U32.15
_CSYNC_B: ER253.1, U12.10, U32.5
_DKRD: ER582.1, R319.1, U3.40
_DKWD: U3.41, U5.70
_DKWDB: ER591.1, U5.65
_DKWEB: ER590.1, U5.64
_DTACK: R113.1, R952.1, U1.10
_DWE: RB152.1, U2.21
_EVEN_CIA: U5.74, U8.25
_FIRE0: ER351.1, U7.10
_FIRE1: ER361.1, U2.78, U7.11
_HLT: RA951.1, U1.19, U5.39
_HSYNC: ER252.1, R251.2, U2.81, U8.21
_IDE_CS[1]: CN16.37, U5.13
_IDE_CS[2]: CN16.38, U5.14
_IDE_IRQ: CN16.31, RX715.1, U5.12
_IDE_LED: CN16.39, R631.2, R632.1
_INDEX: D574.2, ER596.1, R512.2, U8.26
_INT2: P9.63, RB954.1, U3.19, U5.84, U7.23
_INT3: U2.17, U3.20
_INT6: P9.64, RA954.1, U3.21, U5.83, U8.23
_IORD: CN16.25, P9.71, U5.19, U43.16
_IOWR: CN16.23, P9.72, U5.18, U43.15
_IPL0: RA953.1, U1.27, U3.13
_IPL1: RB953.1, U1.26, U3.14
_IPL2: RC953.1, U1.25, U3.15
_KB_CLOCK: RA511.2, U7.44, U13.41
_KB_DATA: RB511.2, U7.43, U13.42
_KB_RESET: Q511.3, RD511.2, U5.63, U49.1
_LDS: RC951.1, U1.8, U2.51, U5.35, U43.13
_LED: R635.2, R636.1, U7.3, U28.2
_MTR: U5.71, U8.19
_MTR0: ER599.1, R633.2, R634.1, U5.67
_MTRX: ER583.1, U5.68
_NET_CS: P9.61, U5.16
_ODD_CIA: U5.73, U7.25
_OE: U5.9, U6.13, U43.18
_RAS[0]: RC152.1, U2.57
_RAS[1]: RD152.1, U2.56
_RDY: ER581.1, U7.9
_REG: U5.7, U43.12, U44.12
_RESET: CN16.1, ER525.2, ER585.1, P9.70, U32.3
_ROE: P9.40, R161.1, U16.27, U17.27
_ROMEN: U5.21, U6.11
_RST: RB951.1, U1.20, U2.16, U3.11, U5.40, U7.37, U8.37, U13.43, U32.17
_RTC_CS: P9.73, U5.17
_RXD: U3.44, U29.3
_SEL0: ER580.1, U5.72, U8.15
_SEL1: ER595.1, U8.16
_SEL2: ER584.1, U8.17
_SEL3: ER594.1, U8.18
_SIDE: ER587.1, U8.14
_SPARE_CS: P9.62, U5.15
_STEP: ER592.1, U8.12
_TRK0: ER589.1, U7.8
_TXD: U3.43, U28.9
_UDS: RD951.1, U1.7, U2.52, U5.34, U43.14
_VSYNC: ER251.1, U2.79, U7.21
_WAIT: CN16.27, RG715.2, U5.81, U43.9
_WE: U5.8, U43.17
_WPROT: ER588.1, U7.7
_X1M: P9.75, R162.1
_XCLKEN: EC261.1, ER261.1, R252.2, U25.1

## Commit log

2020-10-12 Add files via upload
    Initial Kicad repository uploaded.
    DESIGN IS CURRENTLY UNTESTED BUT PCBS HAVE BEEN ASSEMBLED
2021-02-23 Add files via upload
    A slightly modified design, that removes the RF modulator and fits an S-Video connector in the space. It utilises the CXA2075 video encoder to create the S-video output and removes the need for the b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
    This design has been tested and is working.
